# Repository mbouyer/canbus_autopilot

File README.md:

# canbus_autopilot
this is a canbus-connected marine autopilot, composed of 3 main parts:
* an IMU, implementing a MARG algorithm and transmitting attitude and rate of turn PGNs
* a display unit, allowing the user to display and change parameters of the autopilot
* a command unit, which is the autopilot itself. It drives the rudder's motor (in my case, and old Autohelm 2000 tiller).

These parts are built around a pic18f26j50, for its low power and native can support. The CAN protocol is based on J1939 and reuses NMEA2000 PGNs when possible.

There is also wxpilot, a wxwidget/socketcan utility which allows to show and change some of the autopilot's parameters from a unix computer (see my marine_charplotter repository)

The display unit can also decode and display navigation PGNs sent by my nmea2000_pi OpenCPN plugin.

I use this hardware for sailing since several years now

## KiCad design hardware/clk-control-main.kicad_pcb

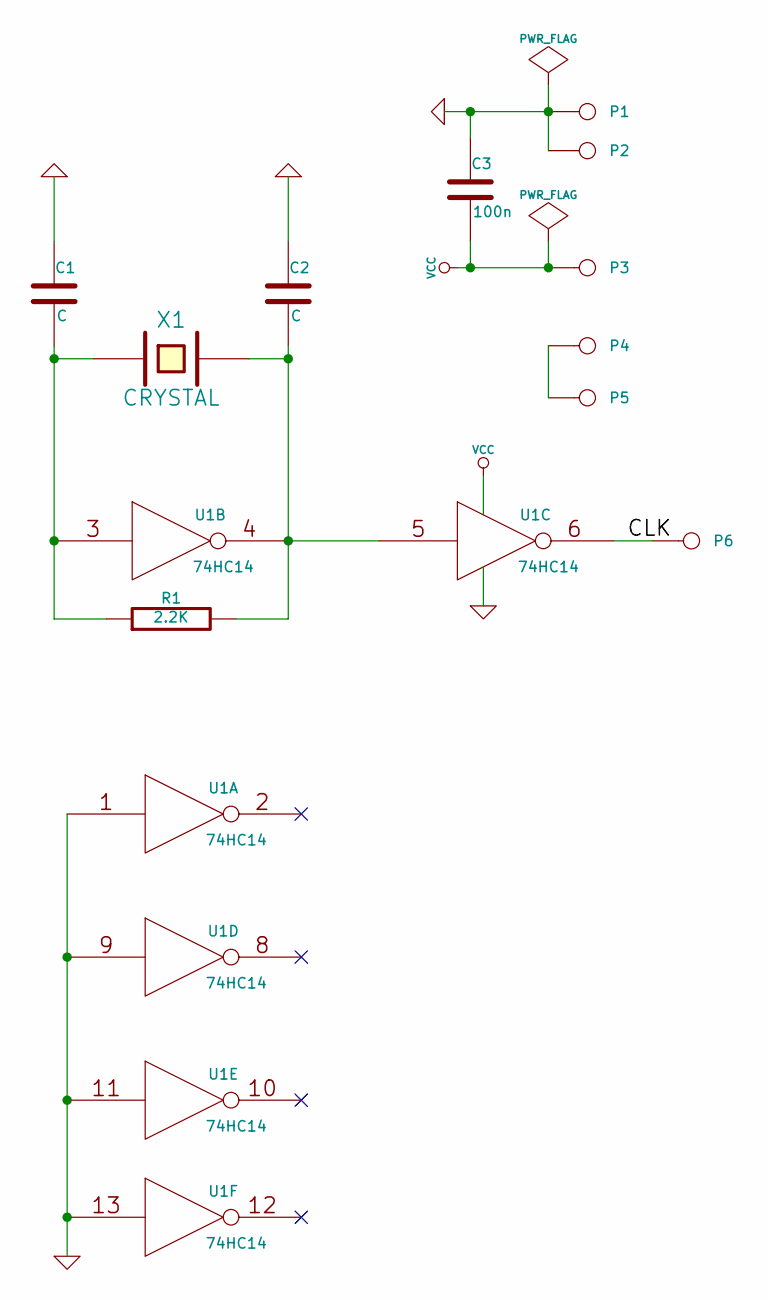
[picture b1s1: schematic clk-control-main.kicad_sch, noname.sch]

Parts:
C1, C2: C
C3: 100n
P1, P2, P3, P4, P5, P6: CONN_1
R1: 2.2K
U1: 74HC14
X1: CRYSTAL

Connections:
/CLK: P6.1, U1.6
GND: C1.1, C2.1, C3.1, P1.1, P2.1, U1.1, U1.7 (GND), U1.9, U1.11, U1.13
unnamed: P4.1, P5.1
unnamed: C2.2, R1.2, U1.4, U1.5, X1.2
unnamed: C1.2, R1.1, U1.3, X1.1
VCC: C3.2, P3.1, U1.14 (VCC)

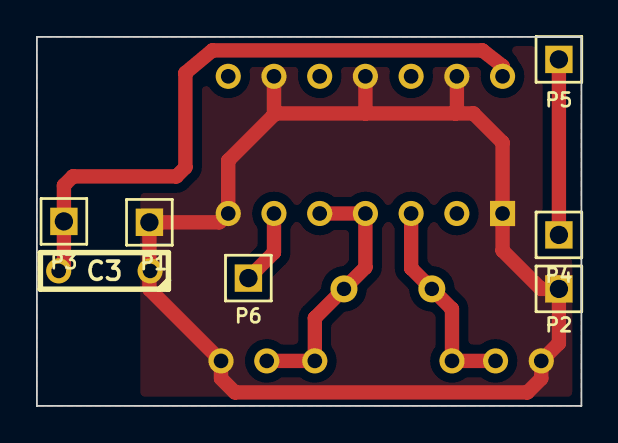
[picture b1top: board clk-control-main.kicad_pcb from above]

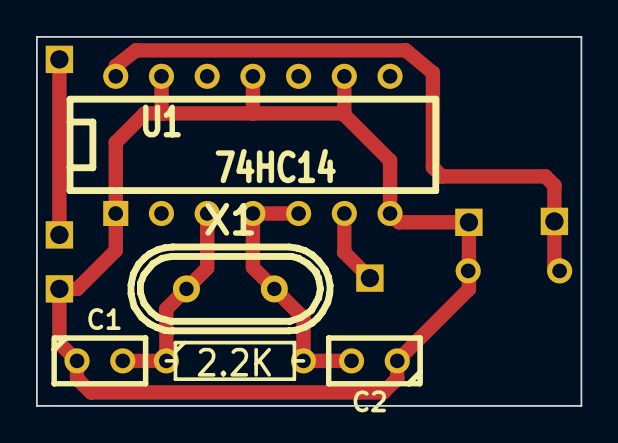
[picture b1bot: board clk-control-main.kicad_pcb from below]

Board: 2 copper layers, 30.2 x 20.5 mm, 12 parts (5 on the bottom side), 6 nets.

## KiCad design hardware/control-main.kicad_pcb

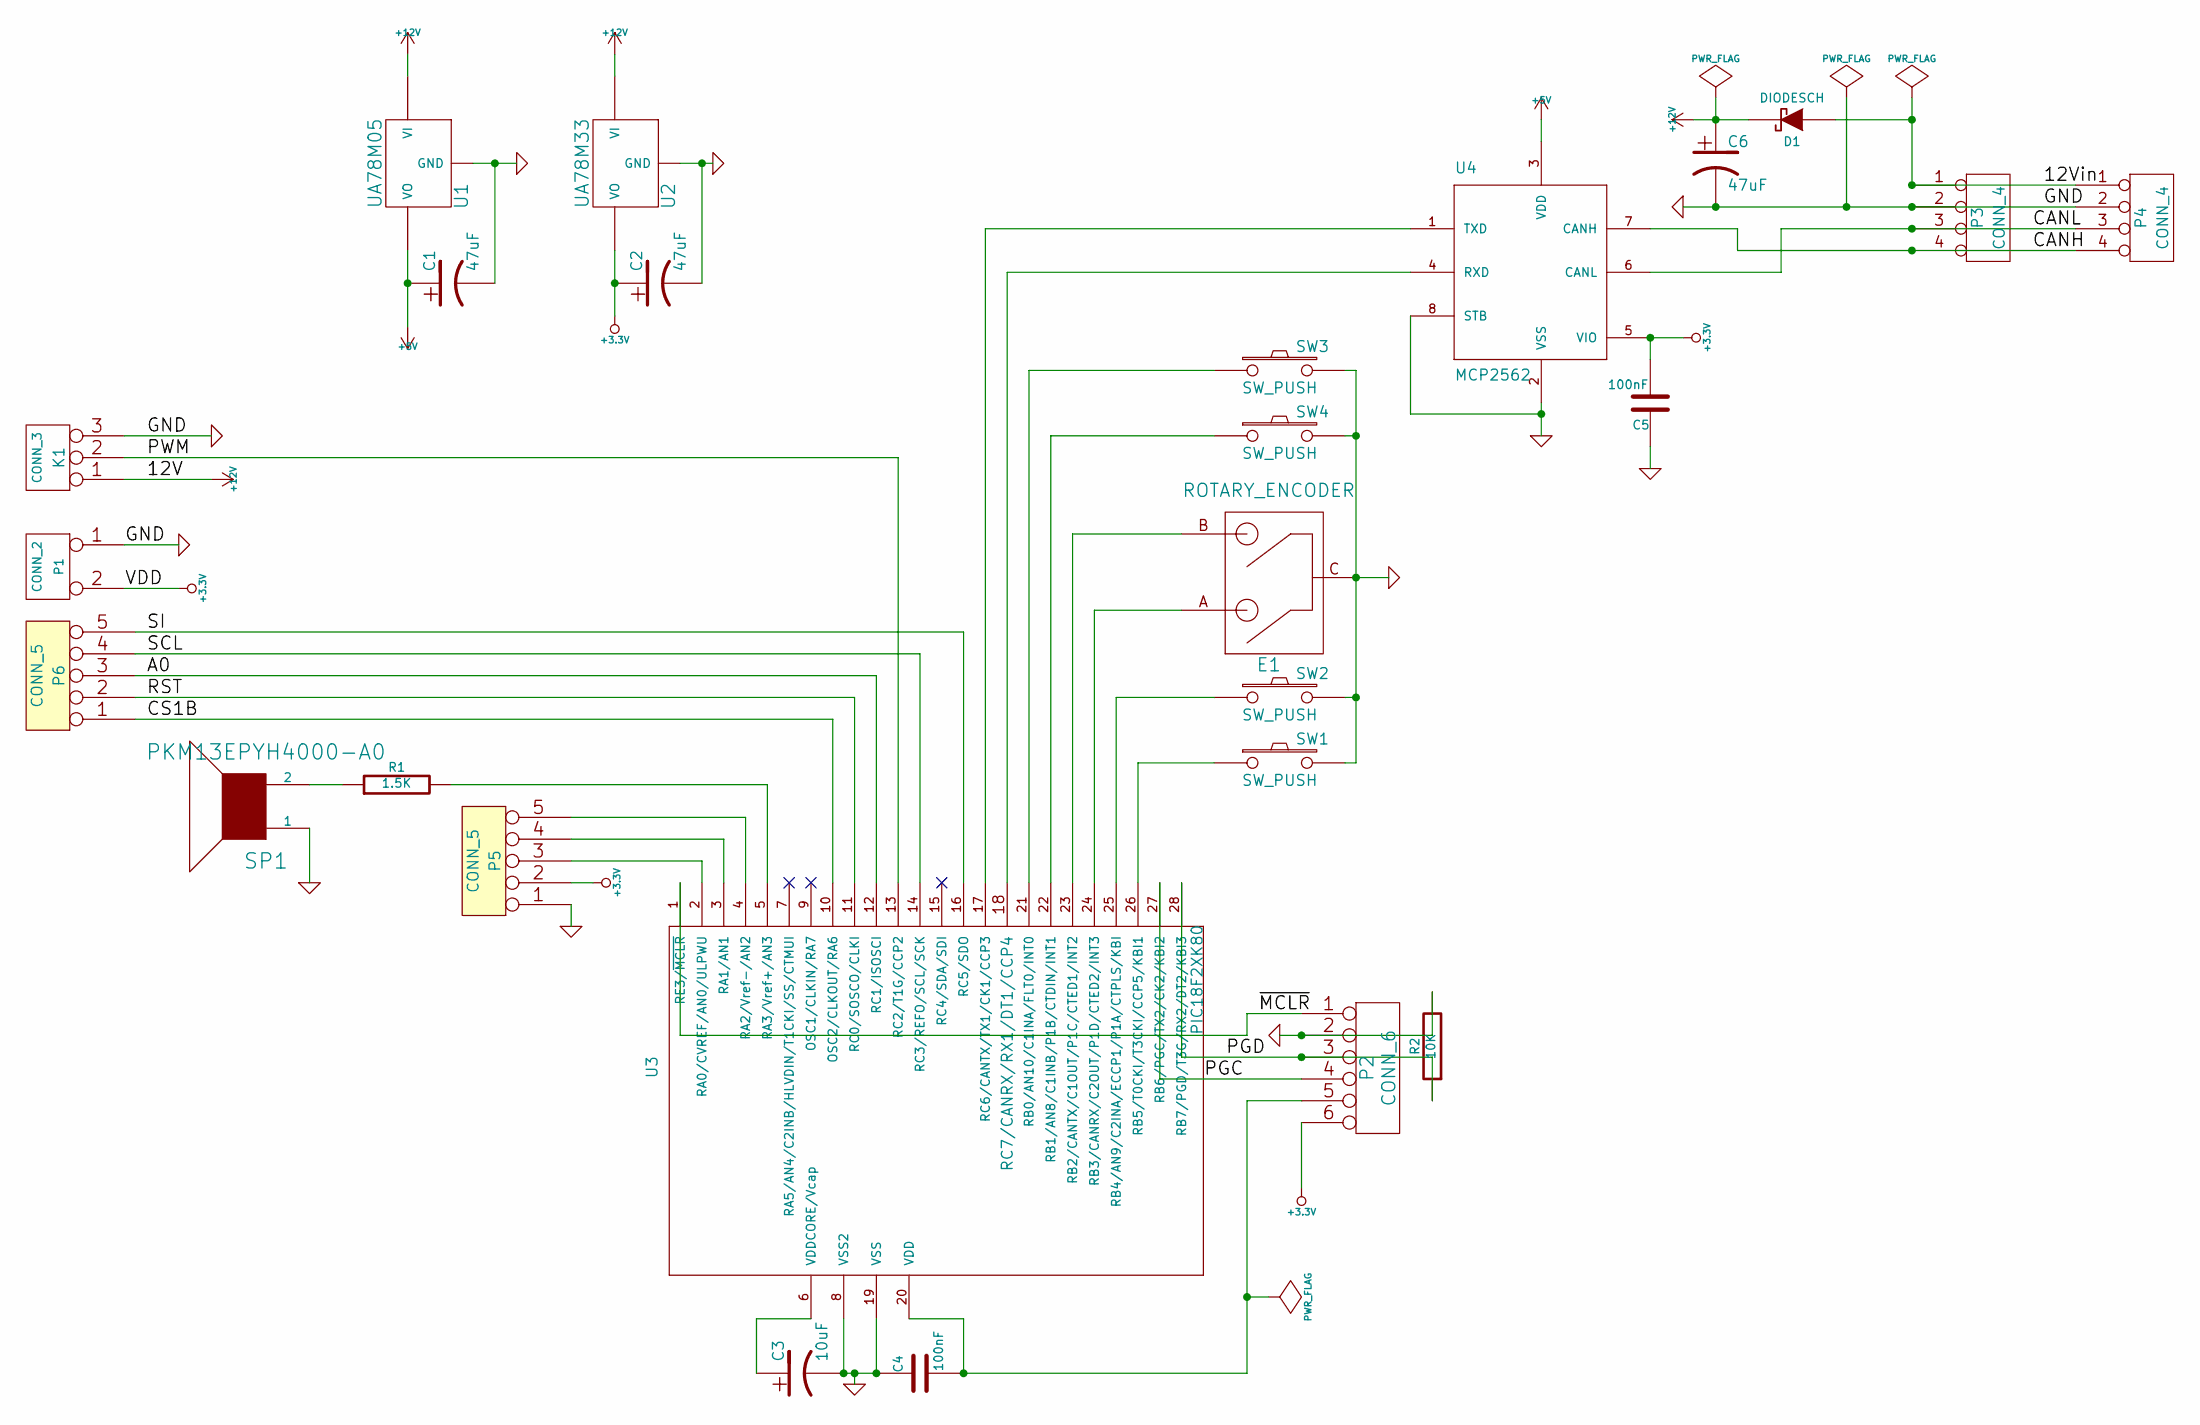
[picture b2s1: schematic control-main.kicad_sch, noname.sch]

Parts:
C1, C2, C6: 47uF
C3: 10uF
C4, C5: 100nF
D1: DIODESCH
E1: ROTARY_ENCODER
K1: CONN_3
P1: CONN_2
P2: CONN_6
P3, P4: CONN_4
P5, P6: CONN_5
R1: 1.5K
R2: 10K
SP1: PKM13EPYH4000-A0
SW1, SW2, SW3, SW4: SW_PUSH
U1: UA78M05
U2: UA78M33
U3: PIC18F2XK80
U4: MCP2562

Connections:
+3.3V: C2.1, C5.2, P1.2 (PM), P2.6, P5.2, U2.3 (VO), U4.5 (VIO)
+5V: C1.1, U1.3 (VO), U4.3 (VDD)
/A0: P6.3, U3.12 (RC1/ISOSCI)
/CANH: P3.4, P4.4, U4.7 (CANH)
/CANL: P3.3, P4.3, U4.6 (CANL)
/CS1B: P6.1, U3.10 (OSC2/CLKOUT/RA6)
/PGC: P2.4, U3.27 (RB6/PGC/TX2/CK2/KBI2)
/PGD: P2.3, R2.1, U3.28 (RB7/PGD/T3G/RX2/DT2/KBI3)
/PWM: K1.2 (PM), U3.13 (RC2/T1G/CCP2)
/RST: P6.2, U3.11 (RC0/SOSCO/CLKI)
/SCL: P6.4, U3.14 (RC3/REFO/SCL/SCK)
/SI: P6.5, U3.16 (RC5/SDO)
/~MCLR: P2.1, U3.1 (RE3/~MCLR)
unnamed: U3.17 (RC6/CANTX/TX1/CK1/CCP3), U4.1 (TXD)
unnamed: U3.18 (RC7/CANRX/RX1/DT1/CCP4), U4.4 (RXD)
unnamed: E1.B, U3.23 (RB2/CANTX/C1OUT/P1C/CTED1/INT2)
unnamed: C3.1, U3.6 (VDDCORE/Vcap)
unnamed: R1.2, U3.5 (RA3/Vref+/AN3)
unnamed: R1.1, SP1.2
unnamed: E1.A, U3.24 (RB3/CANRX/C2OUT/P1D/CTED2/INT3)
unnamed: SW3.1, U3.21 (RB0/AN10/C1INA/FLT0/INT0)
unnamed: P5.3, U3.2 (RA0/CVREF/AN0/ULPWU)
unnamed: SW2.1, U3.25 (RB4/AN9/C2INA/ECCP1/P1A/CTPLS/KBI)
unnamed: SW1.1, U3.26 (RB5/T0CKI/T3CKI/CCP5/KBI1)
unnamed: SW4.1, U3.22 (RB1/AN8/C1INB/P1B/CTDIN/INT1)
unnamed: P5.4, U3.3 (RA1/AN1)
unnamed: P5.5, U3.4 (RA2/Vref-/AN2)

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
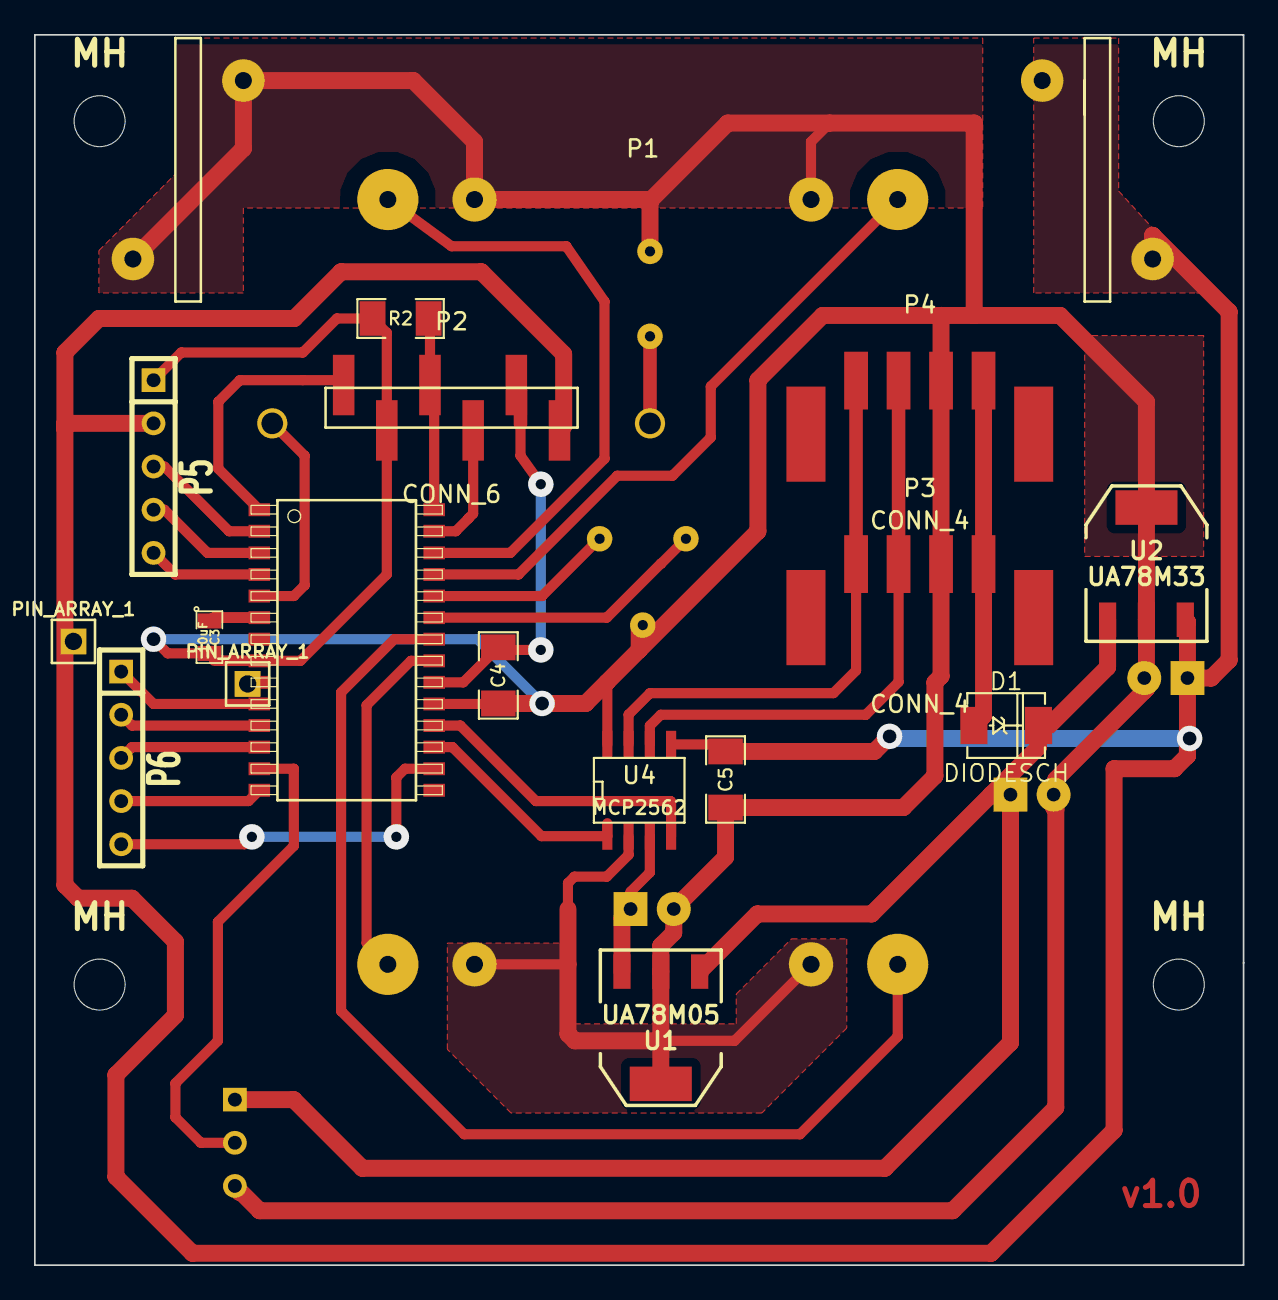
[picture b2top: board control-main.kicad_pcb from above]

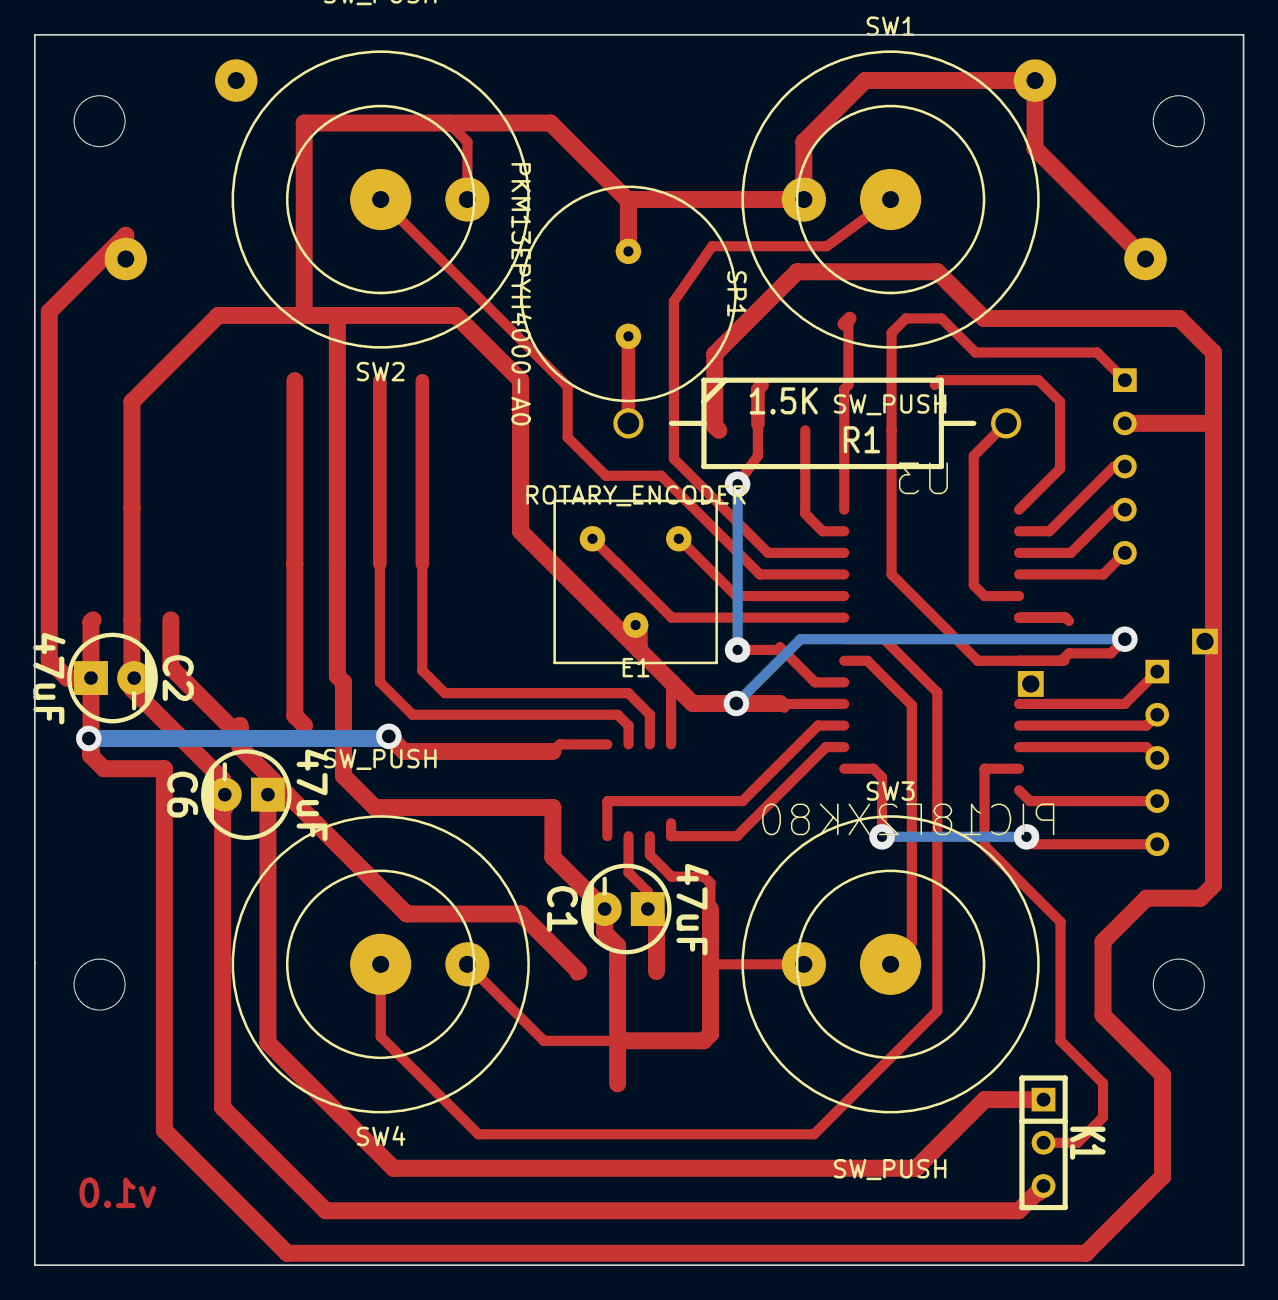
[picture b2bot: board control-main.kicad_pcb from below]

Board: 2 copper layers, 71.1 x 72.4 mm, 32 parts (11 on the bottom side), 31 nets.

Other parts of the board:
MH: MountingHole_3mm_RevA_Date21Jun2010
MH#2, MH#3, MH#4: MountingHole_3mm_RevA_Date21Jun2010
PIN_ARRAY_1, PIN_ARRAY_1#2: Val**; PIN_ARRAY_1

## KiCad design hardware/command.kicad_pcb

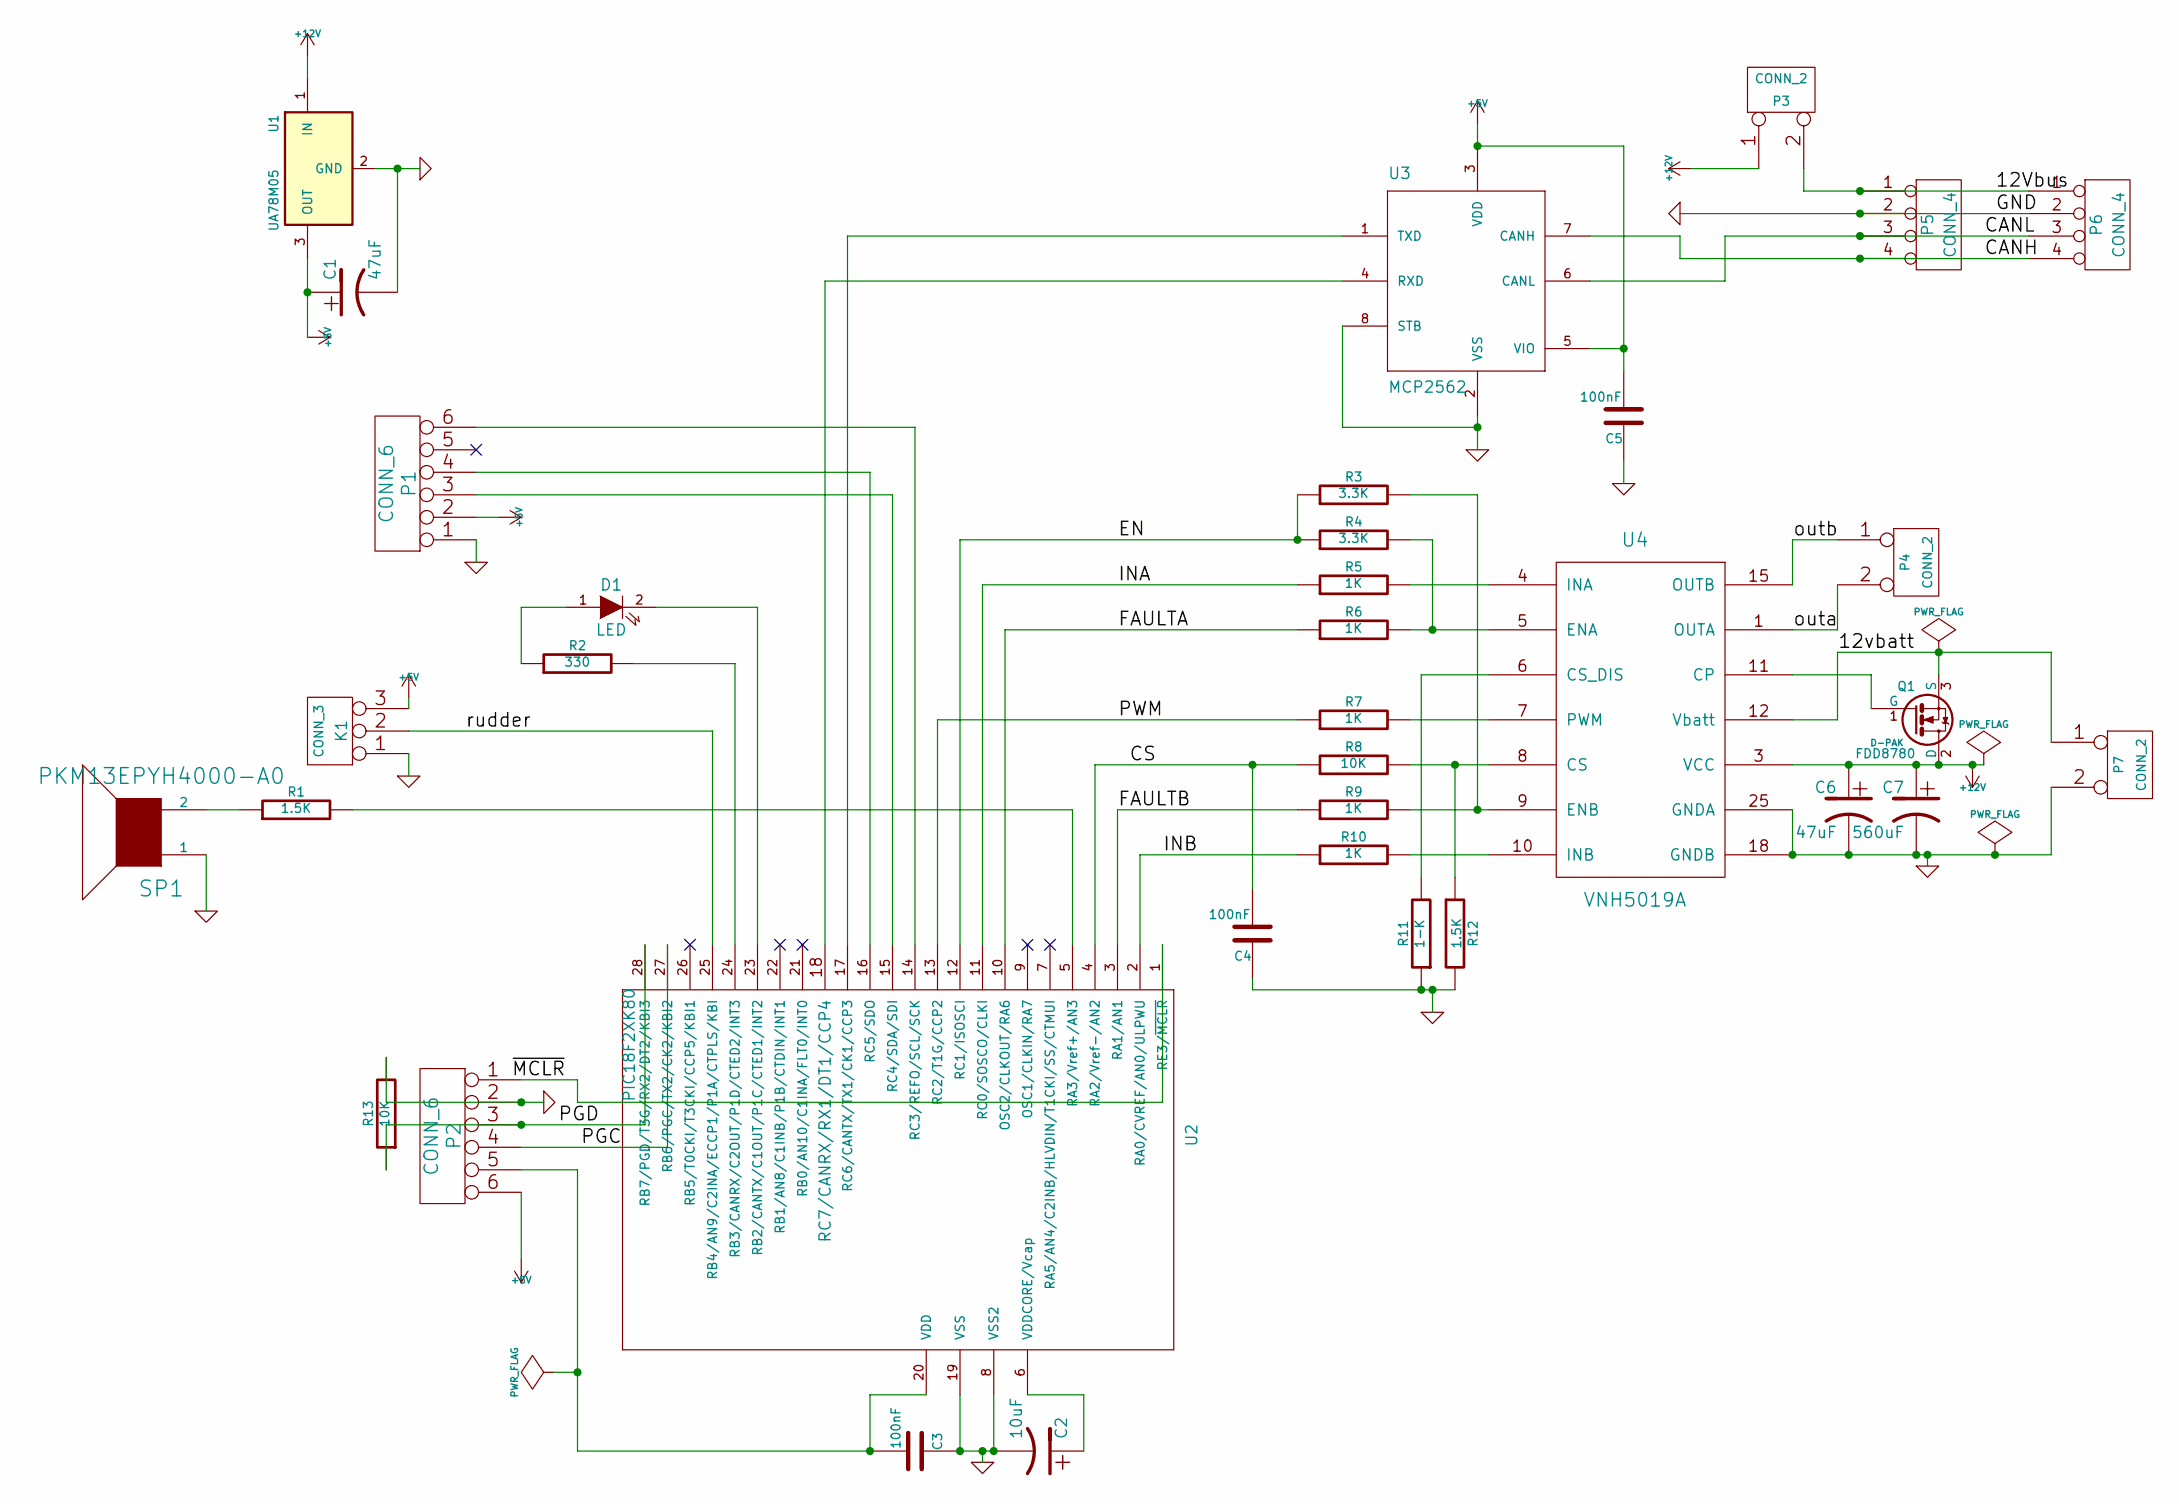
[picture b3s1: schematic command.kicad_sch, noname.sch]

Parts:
C1, C6: 47uF
C2: 10uF
C3, C4, C5: 100nF
C7: 560uF
D1: LED
K1: CONN_3
P1, P2: CONN_6
P3, P4, P7: CONN_2
P5, P6: CONN_4
Q1: FDD8780; D-PAK
R1, R12: 1.5K
R2: 330
R3, R4: 3.3K
R5, R6, R7, R9, R10: 1K
R8, R13: 10K
R11: 1-K
SP1: PKM13EPYH4000-A0
U1: UA78M05
U2: PIC18F2XK80
U3: MCP2562
U4: VNH5019A

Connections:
+5V: C1.1, C5.2, K1.3, P1.2, P2.6, U1.3 (OUT), U3.3 (VDD), U3.5 (VIO)
/12Vbus: P3.2 (PM), P5.1, P6.1
/CANH: P5.4, P6.4, U3.7 (CANH)
/CANL: P5.3, P6.3, U3.6 (CANL)
/CS: C4.2, R8.1, U2.4 (RA2/Vref-/AN2)
/EN: R3.1, R4.1, U2.12 (RC1/ISOSCI)
/FAULTA: R6.1, U2.10 (OSC2/CLKOUT/RA6)
/FAULTB: R9.1, U2.3 (RA1/AN1)
/INA: R5.1, U2.11 (RC0/SOSCO/CLKI)
/INB: R10.1, U2.2 (RA0/CVREF/AN0/ULPWU)
/PGC: P2.4, U2.27 (RB6/PGC/TX2/CK2/KBI2)
/PGD: P2.3, R13.1, U2.28 (RB7/PGD/T3G/RX2/DT2/KBI3)
/PWM: R7.1, U2.13 (RC2/T1G/CCP2)
/outa: P4.2 (PM), U4.1 (OUTA)
/outb: P4.1, U4.15 (OUTB)
/rudder: K1.2 (PM), U2.25 (RB4/AN9/C2INA/ECCP1/P1A/CTPLS/KBI)
/~MCLR: P2.1, U2.1 (RE3/~MCLR)
unnamed: C2.1, U2.6 (VDDCORE/Vcap)
unnamed: R1.2, U2.5 (RA3/Vref+/AN3)
unnamed: R1.1, SP1.2
unnamed: Q1.1 (G), U4.11 (CP)
unnamed: P1.3, U2.15 (RC4/SDA/SDI)
unnamed: P1.4, U2.16 (RC5/SDO)
unnamed: U2.18 (RC7/CANRX/RX1/DT1/CCP4), U3.4 (RXD)
unnamed: D1.2 (K), U2.23 (RB2/CANTX/C1OUT/P1C/CTED1/INT2)
unnamed: R2.2, U2.24 (RB3/CANRX/C2OUT/P1D/CTED2/INT3)
unnamed: P1.6, U2.14 (RC3/REFO/SCL/SCK)
unnamed: U2.17 (RC6/CANTX/TX1/CK1/CCP3), U3.1 (TXD)
unnamed: R11.2, U4.6 (CS_DIS)
unnamed: R10.2, U4.10 (INB)
unnamed: R8.2, R12.1, U4.8 (CS)
unnamed: R7.2, U4.7 (PWM)
unnamed: R5.2, U4.4 (INA)
unnamed: R3.2, R9.2, U4.9 (ENB)
unnamed: D1.1 (A), R2.1
unnamed: R4.2, R6.2, U4.5 (ENA)

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
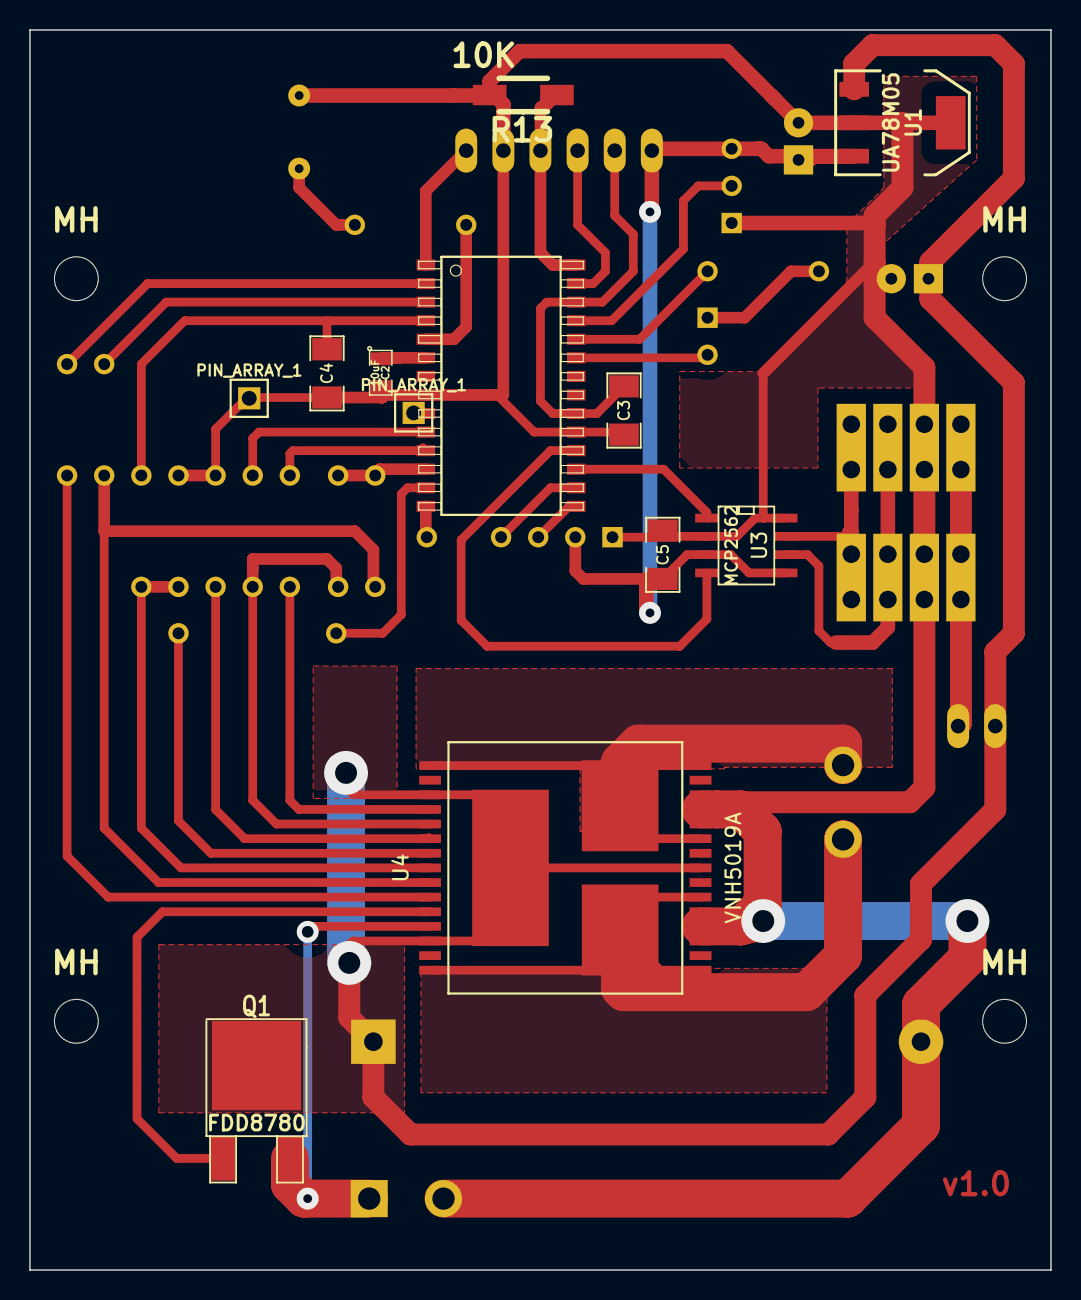
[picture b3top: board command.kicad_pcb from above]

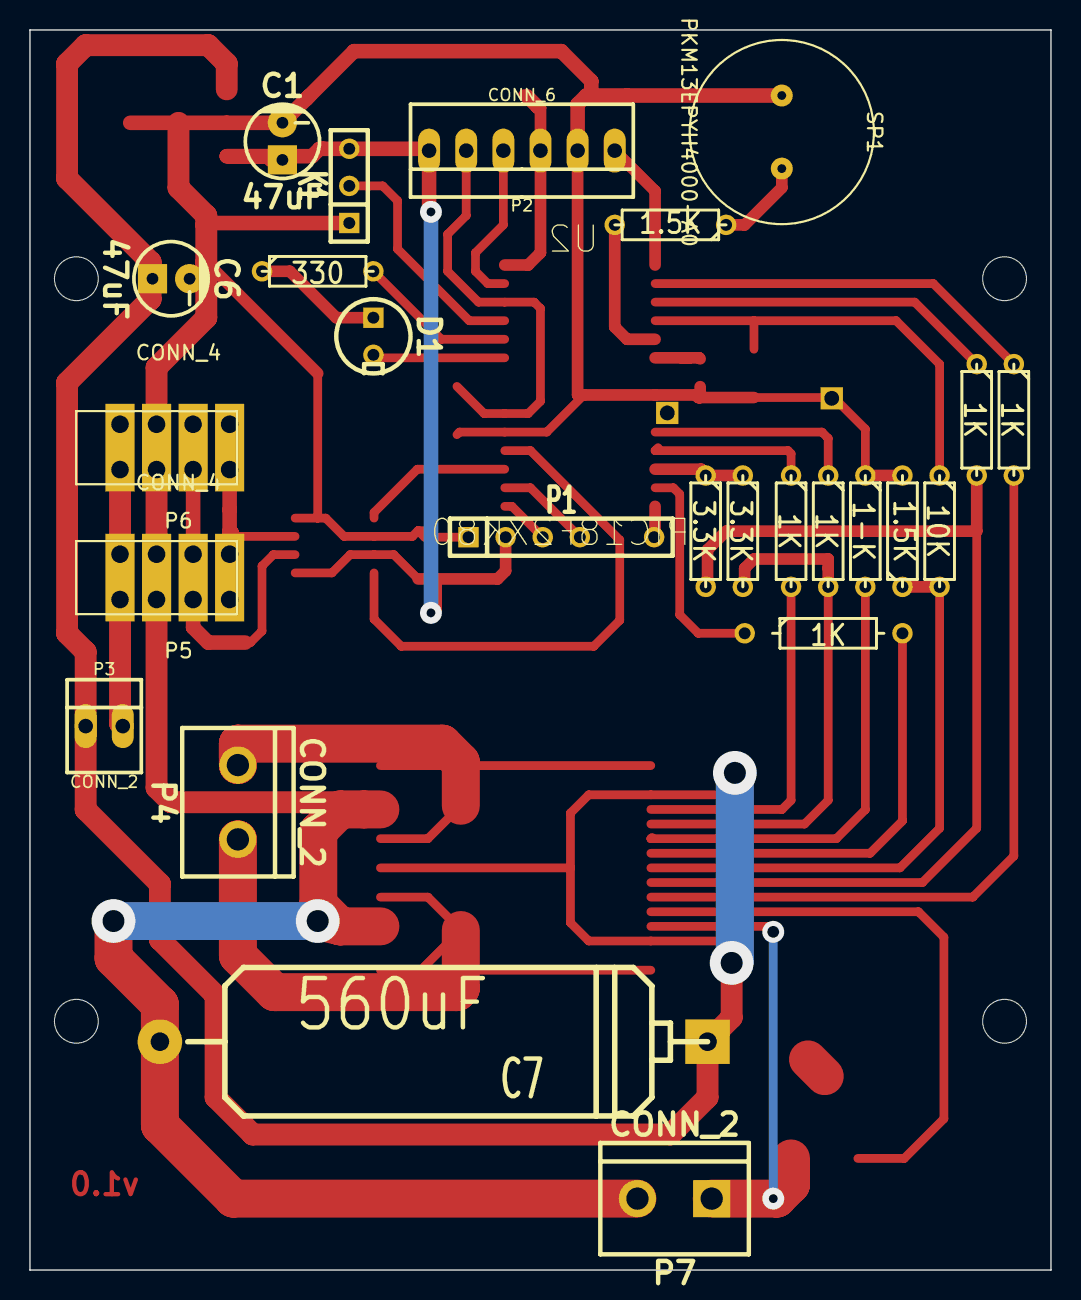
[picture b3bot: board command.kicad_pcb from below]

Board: 2 copper layers, 69.8 x 84.8 mm, 41 parts (25 on the bottom side), 40 nets.

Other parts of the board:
MH: MountingHole_3mm_RevA_Date21Jun2010
MH#2, MH#3, MH#4: MountingHole_3mm_RevA_Date21Jun2010
PIN_ARRAY_1, PIN_ARRAY_1#2: Val**; PIN_ARRAY_1

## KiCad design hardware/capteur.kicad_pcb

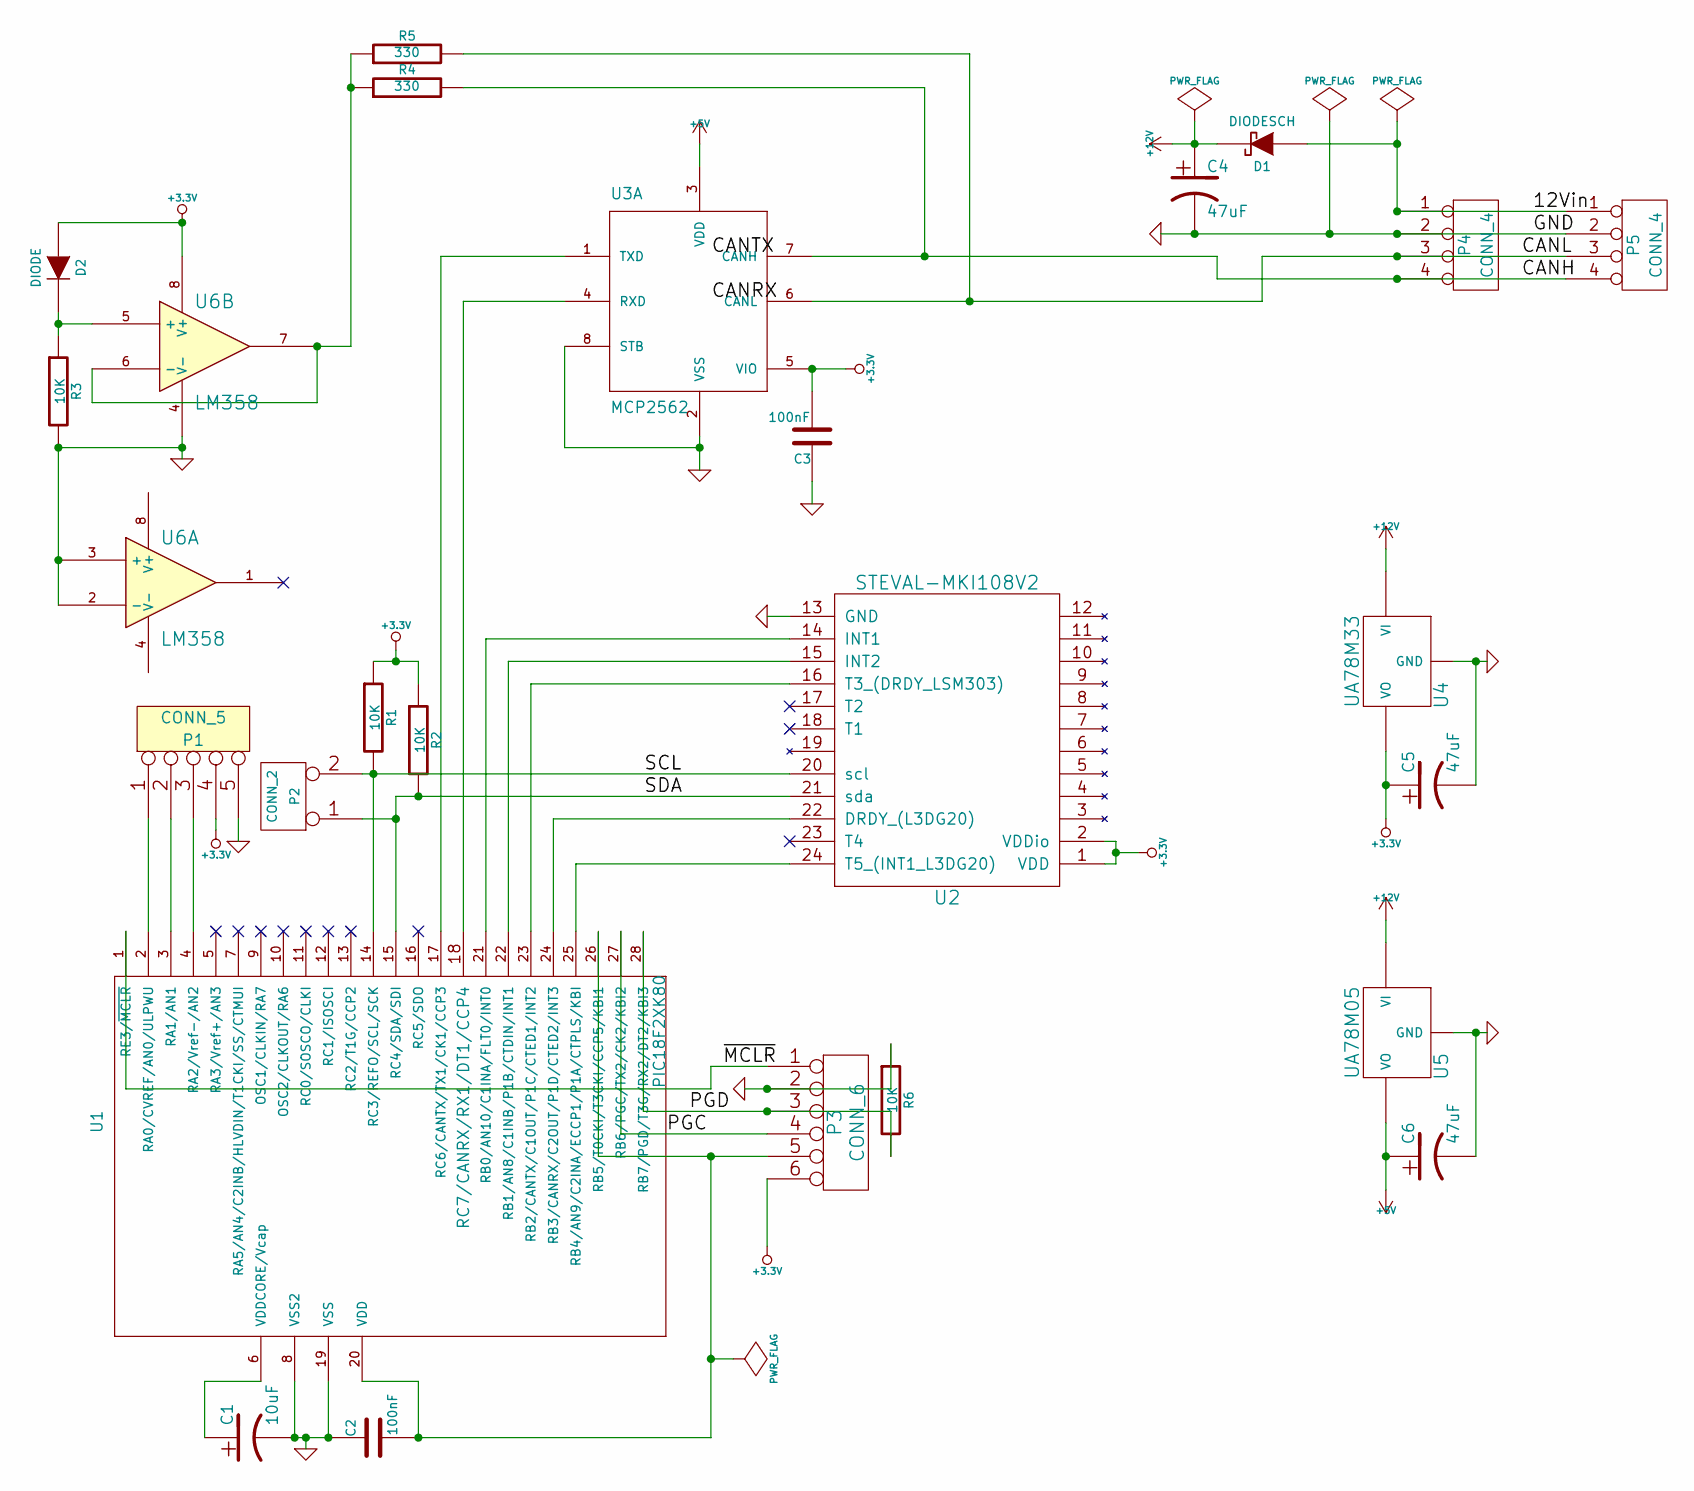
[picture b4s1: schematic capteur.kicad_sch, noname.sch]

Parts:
C1: 10uF
C2, C3: 100nF
C4, C5, C6: 47uF
D1: DIODESCH
D2: DIODE
P1: CONN_5
P2: CONN_2
P3: CONN_6
P4, P5: CONN_4
R1, R2, R3, R6: 10K
R4, R5: 330
U1: PIC18F2XK80
U2: STEVAL-MKI108V2
U3: MCP2562
U4: UA78M33
U5: UA78M05
U6: LM358

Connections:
+3.3V: C3.2, C5.1, D2.1 (A), P1.4, P3.6, R1.1, R2.1, U2.1 (VDD), U2.2 (VDDio), U3.5 (VIO), U4.3 (VO), U6.8 (V+)
+5V: C6.1, U3.3 (VDD), U5.3 (VO)
/CANH: P4.4, P5.4, R4.2, U3.7 (CANH)
/CANL: P4.3, P5.3, R5.2, U3.6 (CANL)
/PGC: P3.4, U1.27 (RB6/PGC/TX2/CK2/KBI2)
/PGD: P3.3, R6.2, U1.28 (RB7/PGD/T3G/RX2/DT2/KBI3)
/SCL: P2.2 (PM), R1.2, U1.14 (RC3/REFO/SCL/SCK), U2.20 (scl)
/SDA: P2.1, R2.2, U1.15 (RC4/SDA/SDI), U2.21 (sda)
/~MCLR: P3.1, U1.1 (RE3/~MCLR)
unnamed: C1.1, U1.6 (VDDCORE/Vcap)
unnamed: U1.17 (RC6/CANTX/TX1/CK1/CCP3), U3.1 (TXD)
unnamed: U1.18 (RC7/CANRX/RX1/DT1/CCP4), U3.4 (RXD)
unnamed: R4.1, R5.1, U6.6 (-), U6.7
unnamed: D2.2 (K), R3.1, U6.5 (+)
unnamed: U1.23 (RB2/CANTX/C1OUT/P1C/CTED1/INT2), U2.16 (T3_(DRDY_LSM303))
unnamed: U1.22 (RB1/AN8/C1INB/P1B/CTDIN/INT1), U2.15 (INT2)
unnamed: U1.21 (RB0/AN10/C1INA/FLT0/INT0), U2.14 (INT1)
unnamed: U1.25 (RB4/AN9/C2INA/ECCP1/P1A/CTPLS/KBI), U2.24 (T5_(INT1_L3DG20))
unnamed: U1.24 (RB3/CANRX/C2OUT/P1D/CTED2/INT3), U2.22 (DRDY_(L3DG20))
unnamed: P1.1, U1.2 (RA0/CVREF/AN0/ULPWU)
unnamed: P1.2, U1.3 (RA1/AN1)
unnamed: P1.3, U1.4 (RA2/Vref-/AN2)

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

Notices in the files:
software/display/main.c:
Copyright (c) 2017 Manuel Bouyer
All rights reserved.
